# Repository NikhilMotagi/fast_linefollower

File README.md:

# fast_linefollower
This autonomous robot is designed to accurately follow a defined black line on a white surface. It utilizes an Arduino Nano microcontroller as its brain, processing sensor data and controlling the robot's movement.

**Key Components:**

- **Microcontroller:** Arduino Nano
- **Sensors:** 8-Array IR Sensor
- **Motor Driver:** TB6612FNG
- **Motors:** N20 12V DC Motors
- **Power Supply:** 12V Battery with LM7805 Voltage Regulator

**Operation:**

1. **Sensor Input:** The 8-array IR sensor continuously scans the surface, detecting the contrast between the black line and the white background.
2. **Signal Processing:** The Arduino Nano processes the analog sensor readings, converting them into digital values.
3. **PID Control:** A Proportional-Integral-Derivative (PID) controller is implemented to regulate the robot's speed and steering. The PID algorithm analyzes the error between the desired line position and the actual position, adjusting the motor speeds accordingly.
4. **Motor Control:** The TB6612FNG motor driver receives commands from the Arduino Nano and controls the direction and speed of the two DC motors.

--- 
### Photo Gallery

| PCB Top View  | PCB Bottom View |
| -------- | ------- |
|  |  |

- Assembled render
  
- IRL
  ||  |
  | ----------| -------------|

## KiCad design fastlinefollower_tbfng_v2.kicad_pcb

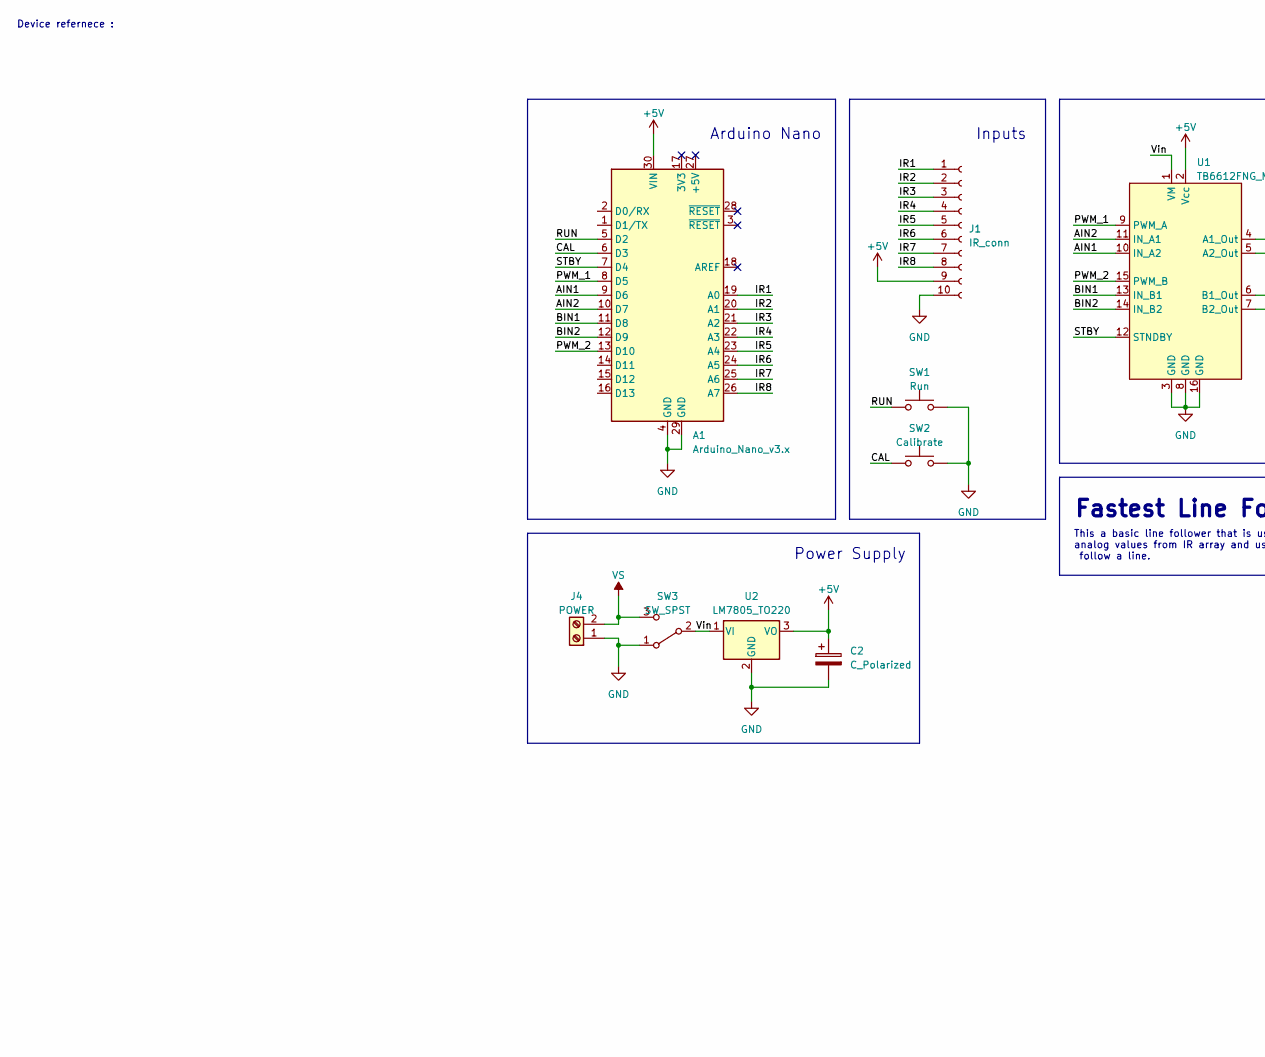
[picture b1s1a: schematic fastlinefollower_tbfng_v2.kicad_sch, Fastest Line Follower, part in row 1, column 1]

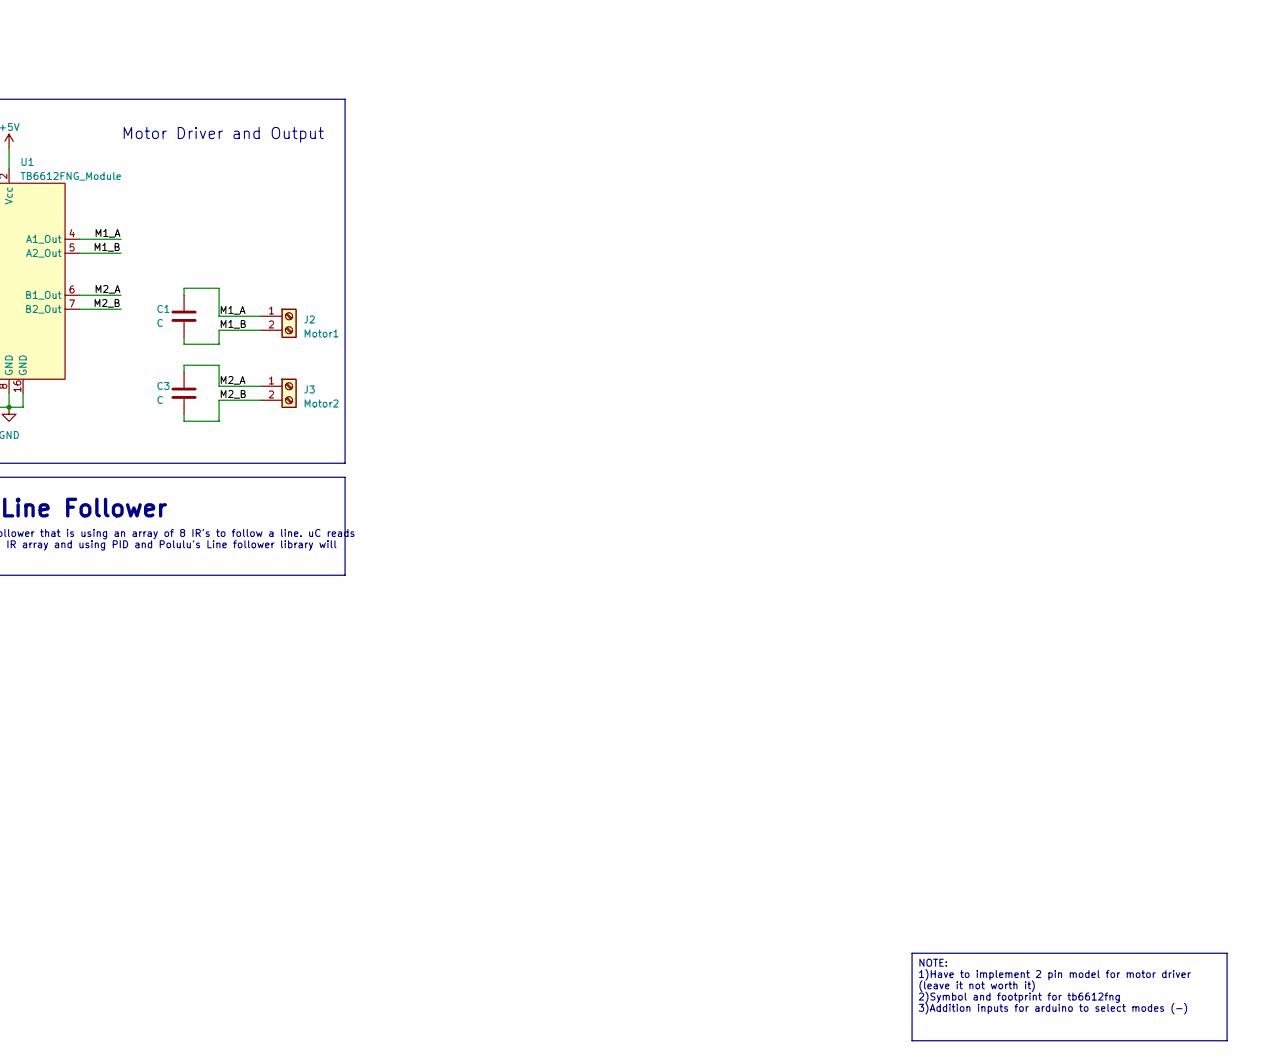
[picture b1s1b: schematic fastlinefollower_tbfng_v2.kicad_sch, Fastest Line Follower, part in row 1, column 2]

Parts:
A1: Arduino_Nano_v3.x; Arduino_Nano
C1, C3: C; C_Disc_D3.4mm_W2.1mm_P2.50mm
C2: C_Polarized; C_Radial_D5.0mm_H7.0mm_P2.00mm
J1: IR_conn; PinSocket_1x10_P2.54mm_Vertical
J2: Motor1; MOTORmount
J3: Motor2; MOTORmount
J4: POWER; TerminalBlock_bornier-2_P5.08mm
SW1: Run; SPST_Pushbutton
SW2: Calibrate; SPST_Pushbutton
SW3: SW_SPST; SPDT_Slidebutton
U1: TB6612FNG_Module; TB1266FNG_Module
U2: LM7805_TO220; TO-220-3_Vertical

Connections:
+5V: A1.30 (VIN), C2.1, J1.9, U1.2 (Vcc), U2.3 (VO)
/AIN1: A1.9 (D6), U1.10 (IN_A2)
/AIN2: A1.10 (D7), U1.11 (IN_A1)
/BIN1: A1.11 (D8), U1.13 (IN_B1)
/BIN2: A1.12 (D9), U1.14 (IN_B2)
/CAL: A1.6 (D3), SW2.1
/IR1: A1.19 (A0), J1.1
/IR2: A1.20 (A1), J1.2
/IR3: A1.21 (A2), J1.3
/IR4: A1.22 (A3), J1.4
/IR5: A1.23 (A4), J1.5
/IR6: A1.24 (A5), J1.6
/IR7: A1.25 (A6), J1.7
/IR8: A1.26 (A7), J1.8
/M1_A: C1.1, J2.1, U1.4 (A1_Out)
/M1_B: C1.2, J2.2, U1.5 (A2_Out)
/M2_A: C3.1, J3.1, U1.6 (B1_Out)
/M2_B: C3.2, J3.2, U1.7 (B2_Out)
/PWM_1: A1.8 (D5), U1.9 (PWM_A)
/PWM_2: A1.13 (D10), U1.15 (PWM_B)
/RUN: A1.5 (D2), SW1.1
/STBY: A1.7 (D4), U1.12 (STNDBY)
/Vin: SW3.2 (B), U1.1 (VM), U2.1 (VI)
GND: A1.4 (GND), A1.29 (GND), C2.2, J1.10, J4.1, SW1.2, SW2.2, SW3.1 (A), U1.3 (GND), U1.8 (GND), U1.16 (GND), U2.2 (GND)
VS: J4.2, SW3.3 (C)

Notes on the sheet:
NOTE: 1)Have to implement 2 pin model for motor driver (leave it not worth it) 2)Symbol and footprint for tb6612fng 3)Addition inputs for arduino to select modes (-)
Device refernece :
Fastest Line Follower
Inputs
Power Supply
Motor Driver and Output
This a basic line follower that is using an array of 8 IR's to follow a line. uC reads analog values from IR array and using PID and Polulu's Line follower library will follow a line.
Arduino Nano

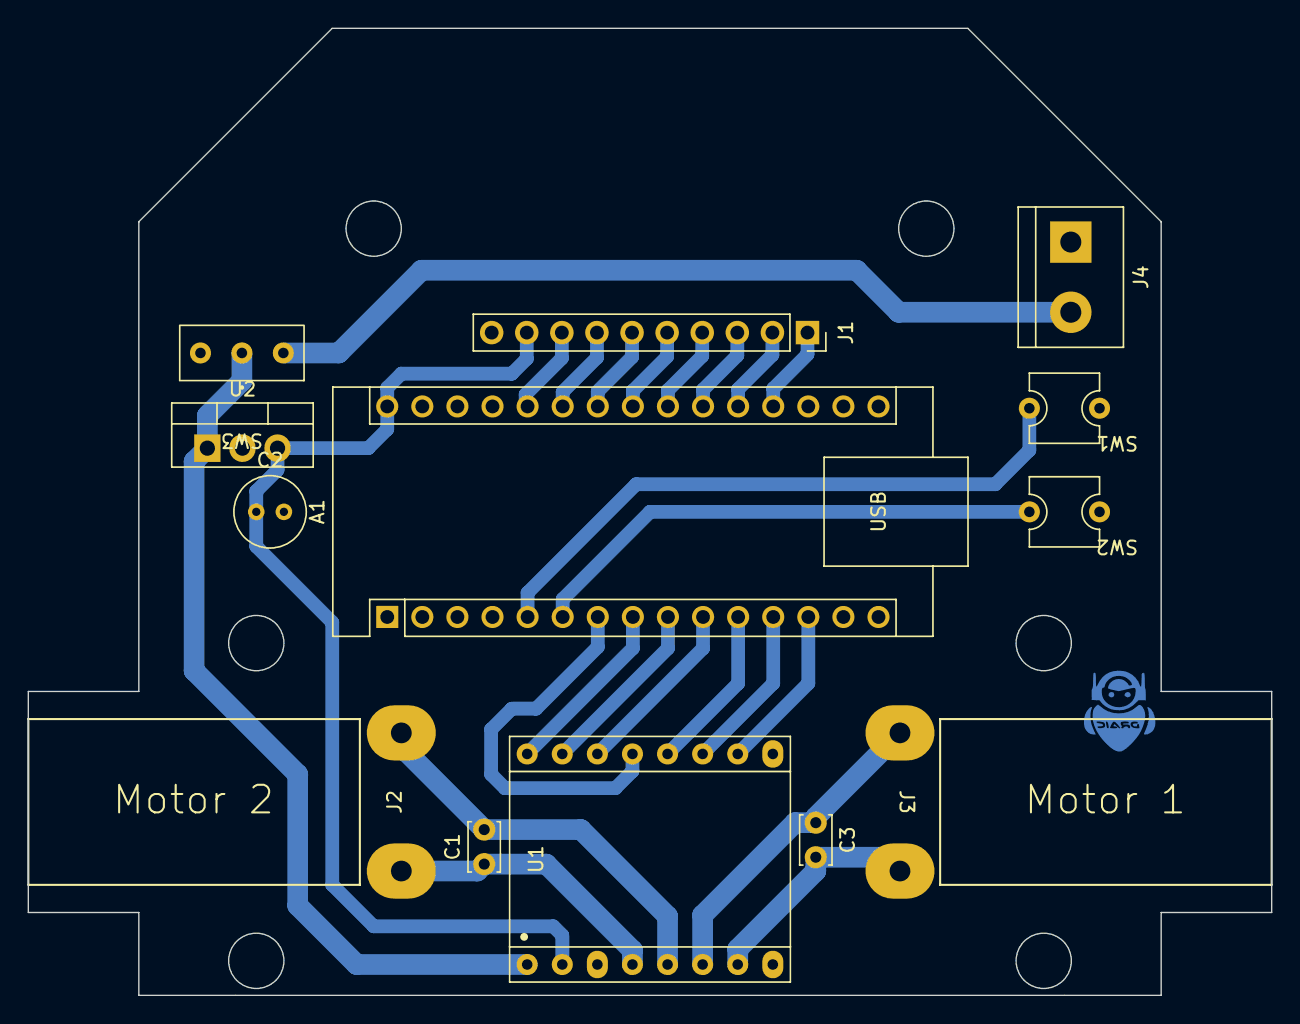
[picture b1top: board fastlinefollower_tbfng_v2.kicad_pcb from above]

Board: 2 copper layers, 90.0 x 70.0 mm, 13 parts (0 on the bottom side), 25 nets.

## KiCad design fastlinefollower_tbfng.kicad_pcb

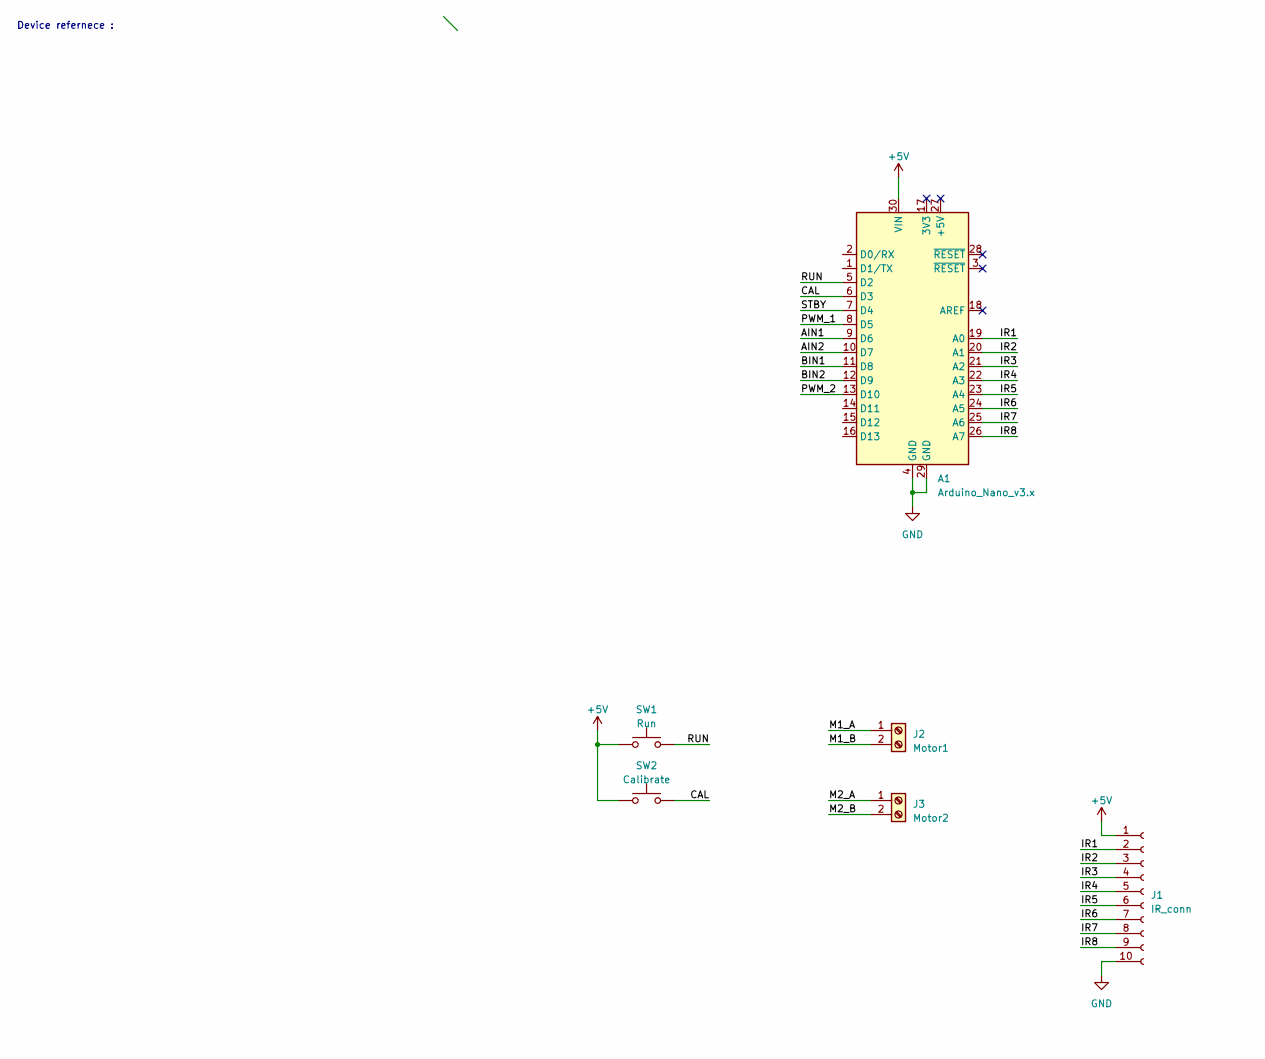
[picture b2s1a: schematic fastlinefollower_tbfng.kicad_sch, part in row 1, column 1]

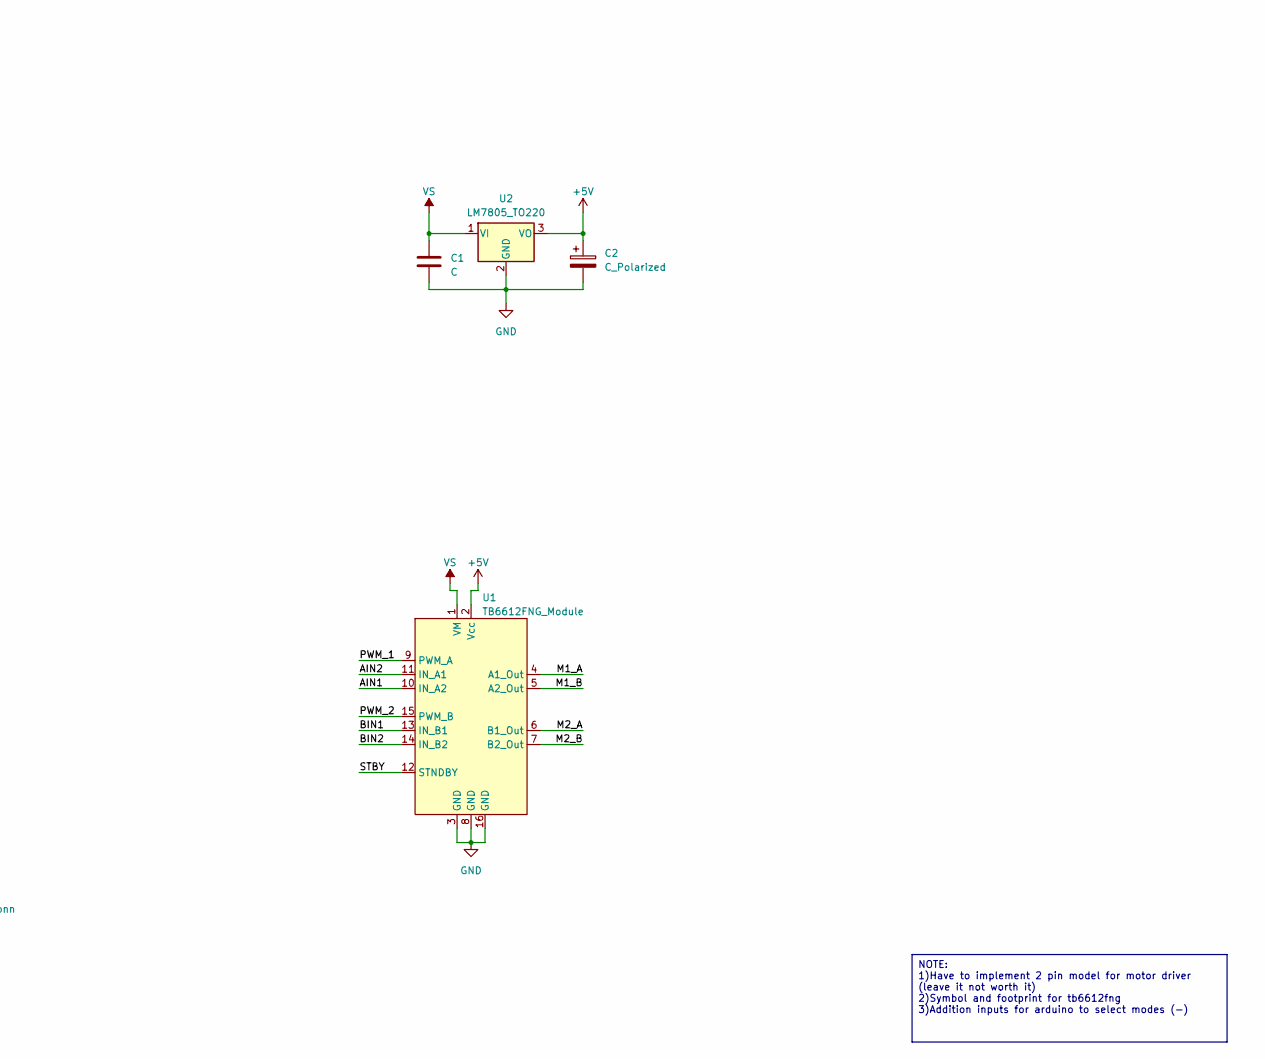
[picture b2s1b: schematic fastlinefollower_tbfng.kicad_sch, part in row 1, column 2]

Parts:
A1: Arduino_Nano_v3.x; Arduino_Nano
C1: C; C_Disc_D5.0mm_W2.5mm_P2.50mm
C2: C_Polarized; C_Radial_D5.0mm_H7.0mm_P2.00mm
J1: IR_conn; PinSocket_1x10_P2.54mm_Vertical
J2: Motor1; TerminalBlock_Altech_AK300-2_P5.00mm
J3: Motor2; TerminalBlock_Altech_AK300-2_P5.00mm
SW1: Run; SW_PUSH_6mm
SW2: Calibrate; SW_PUSH_6mm
U1: TB6612FNG_Module; TB1266FNG_Module
U2: LM7805_TO220; TO-220-3_Vertical

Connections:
+5V: A1.30 (VIN), C2.1, J1.1, SW1.1, SW2.1, U1.2 (Vcc), U2.3 (VO)
/AIN1: A1.9 (D6), U1.10 (IN_A2)
/AIN2: A1.10 (D7), U1.11 (IN_A1)
/BIN1: A1.11 (D8), U1.13 (IN_B1)
/BIN2: A1.12 (D9), U1.14 (IN_B2)
/CAL: A1.6 (D3), SW2.2
/IR1: A1.19 (A0), J1.2
/IR2: A1.20 (A1), J1.3
/IR3: A1.21 (A2), J1.4
/IR4: A1.22 (A3), J1.5
/IR5: A1.23 (A4), J1.6
/IR6: A1.24 (A5), J1.7
/IR7: A1.25 (A6), J1.8
/IR8: A1.26 (A7), J1.9
/M1_A: J2.1, U1.4 (A1_Out)
/M1_B: J2.2, U1.5 (A2_Out)
/M2_A: J3.1, U1.6 (B1_Out)
/M2_B: J3.2, U1.7 (B2_Out)
/PWM_1: A1.8 (D5), U1.9 (PWM_A)
/PWM_2: A1.13 (D10), U1.15 (PWM_B)
/RUN: A1.5 (D2), SW1.2
/STBY: A1.7 (D4), U1.12 (STNDBY)
GND: A1.4 (GND), A1.29 (GND), C1.2, C2.2, J1.10, U1.3 (GND), U1.8 (GND), U1.16 (GND), U2.2 (GND)
VS: C1.1, U1.1 (VM), U2.1 (VI)

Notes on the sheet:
NOTE: 1)Have to implement 2 pin model for motor driver (leave it not worth it) 2)Symbol and footprint for tb6612fng 3)Addition inputs for arduino to select modes (-)
Device refernece :

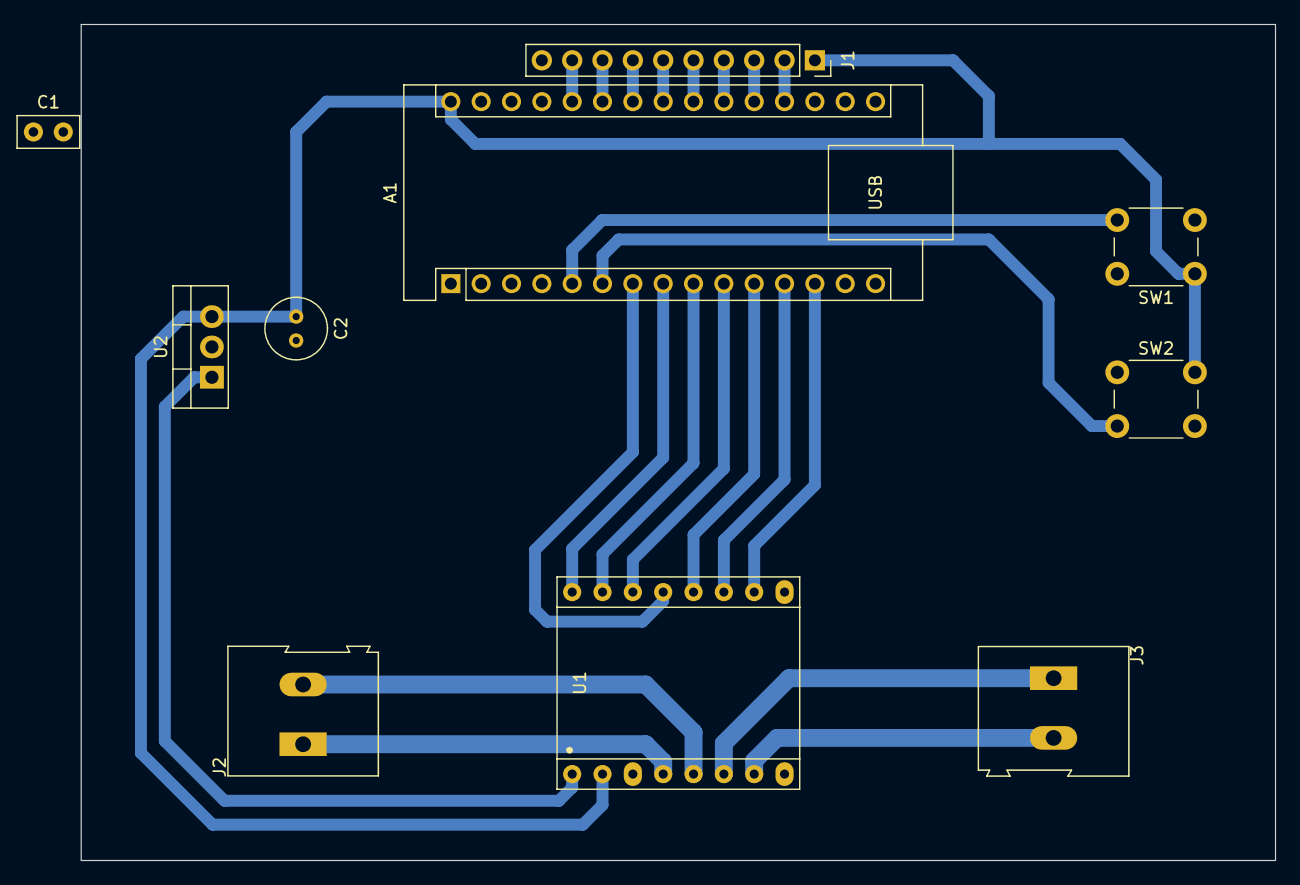
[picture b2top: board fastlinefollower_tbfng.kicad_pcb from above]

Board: 2 copper layers, 100.0 x 70.0 mm, 10 parts (0 on the bottom side), 24 nets.

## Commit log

2023-05-23 tbfng looks good
2023-05-26 updates260523
2023-05-27 Driver symbol added
2023-06-11 basic layout done
2023-06-13 well theres a second version now
2023-06-27 new layout
2023-06-27 added dependencies
2023-07-10 final twicks
2024-11-21 added images for readme
2024-11-21 changed image size
